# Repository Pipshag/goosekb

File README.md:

# Goose  38-key split wireless keyboard
Goose is a keyboard built with the help of [Ergogen](https://github.com/ergogen/ergogen).
This means that it's really simple to edit */config.yaml* and generate your own design, stagger and splay.
The KiCad PCBs are located in *pcb/* and contains the pcb, plate and bottom boards.
Use them to either manufacture directly or take leads from how I routed the pcb if you create your own. 

## Description
Wireless 38-key split and reversible keyboard with two rotary encoders, no support for button/press on these.
Plate is optional, but I'm using 3-pin switches which does almost make plates mandatory.
Batteries soldered directly to PCB, bought batteries with protection against shorts.
All PCBs are reversible.

Stagger and splay according to my hands, helped by [Ergopad](https://pashutk.com/ergopad/).
Artwork generated with Midjourney AI. Not really gooses but goose-like? :D

## Variations
See branches for keyswitch variations (choc and mx).

## Images
Final, completed, keyboard (left side).

Ergogen generated layout.

Routed PCB, KiCad preview.

## Materials
- 2 x Xiao Seeed nRF52840
- 2 x EC12 rotary encoders
- 2 x Knobs for rotary encoder
- 38 x Cherry MX switches
- 38 x SOD-123 Diodes
- 2 x LiPo batteries

## Firmware
ZMK firmware for wireless support. Contained in *firmware/*, includes build-script.

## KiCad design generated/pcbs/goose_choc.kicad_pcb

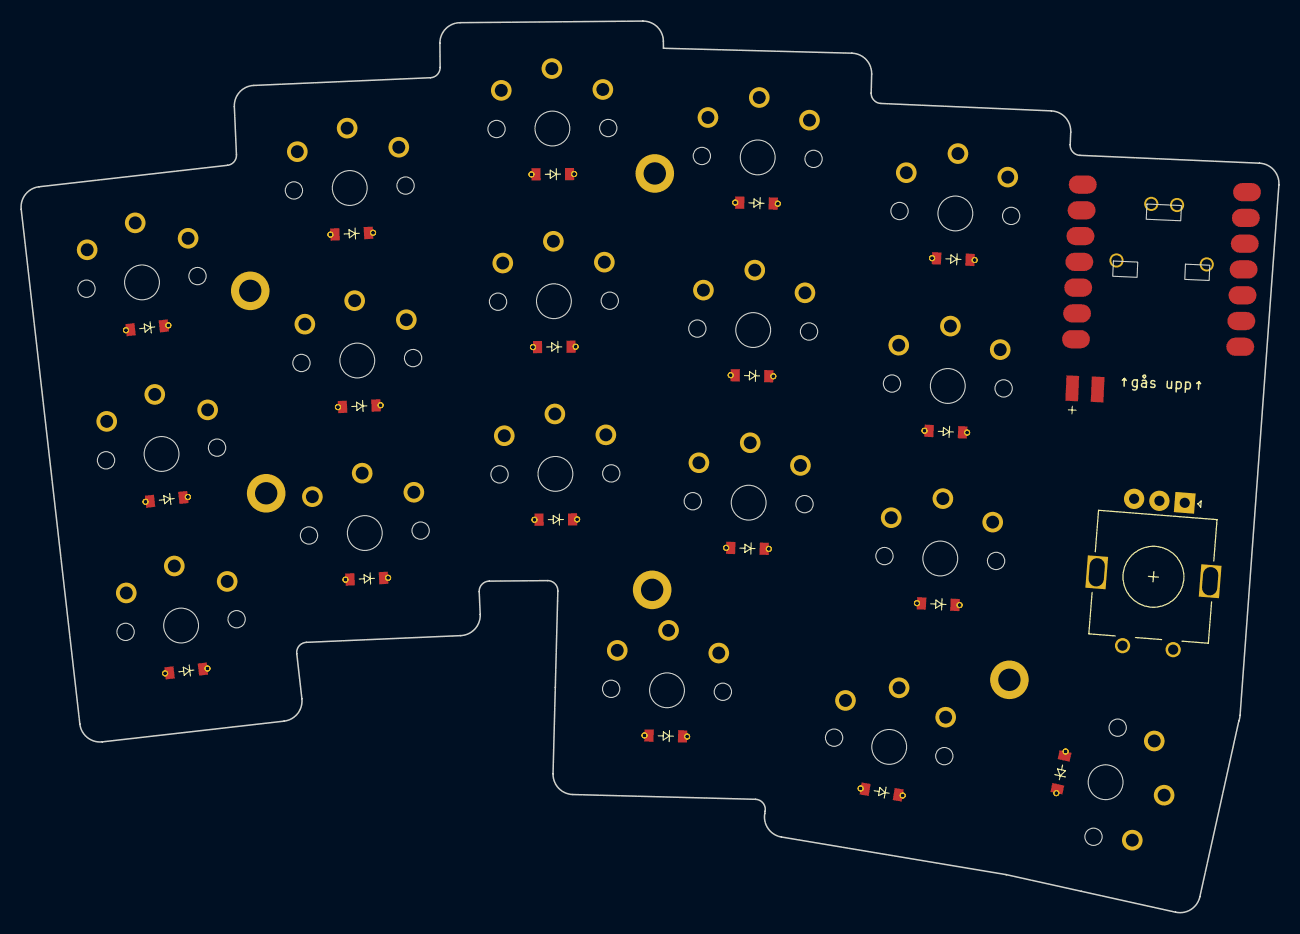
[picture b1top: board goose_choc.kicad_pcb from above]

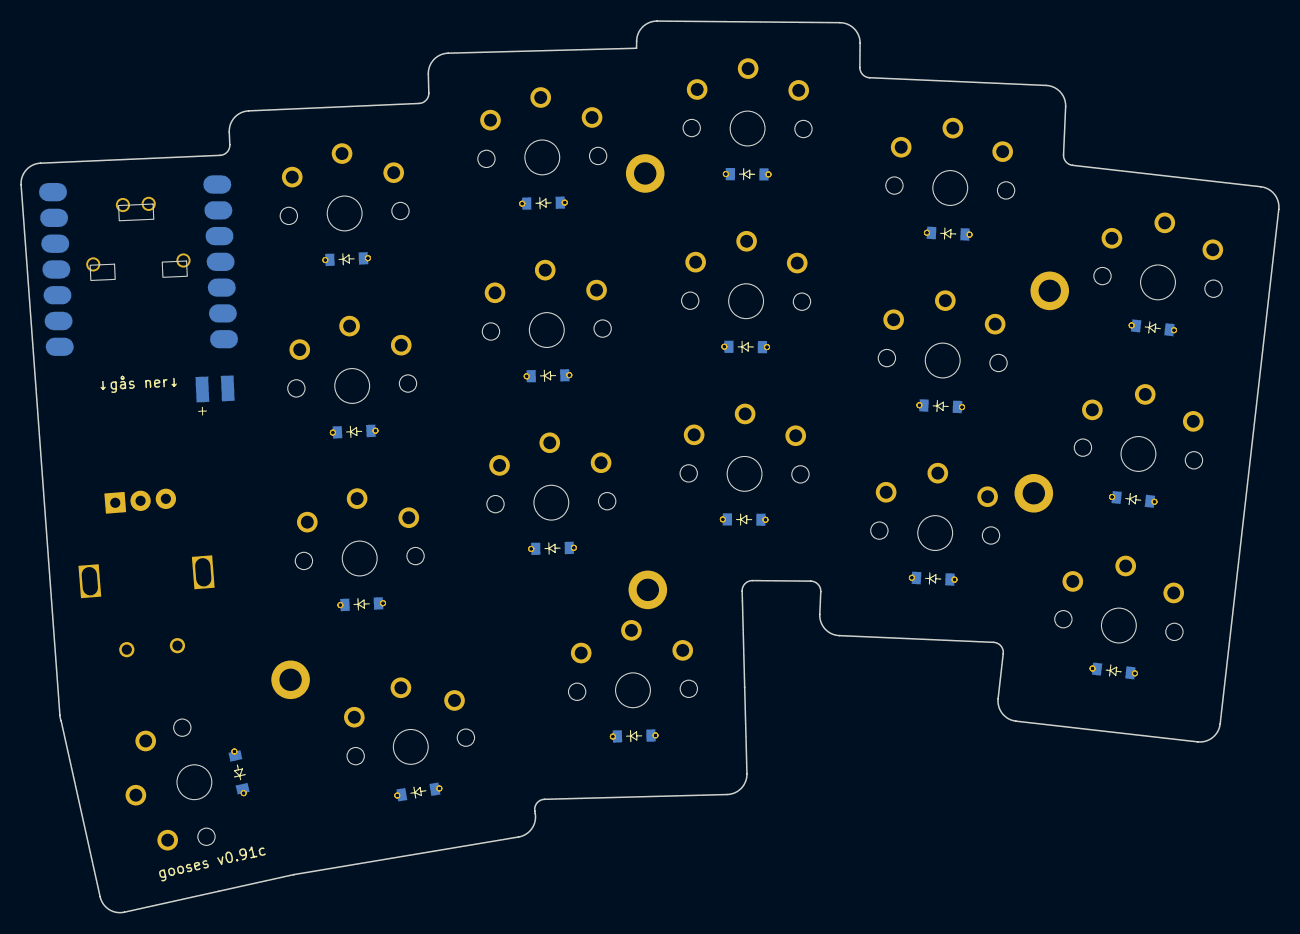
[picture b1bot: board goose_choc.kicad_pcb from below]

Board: 2 copper layers, 123.8 x 87.8 mm, 62 parts (18 on the bottom side), 31 nets, no tracks yet.

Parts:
Di1, Di2, Di3, Di4, Di5, Di6, Di7, Di8, Di9, Di10, Di11, Di12, Di13, Di14, Di15, Di16, Di17, Di18, Di19, Di20, Di21, Di22, Di23, Di24, Di25, Di26, Di27, Di28, Di29, Di30, Di31, Di32, Di33, Di34, Di35, Di36: D_SOD-123
H1, H2, H3, H4, H5: mounting_hole
MCU1: xiao-ble-smd-reversible
PAD1: pads
ROT1: rotary_encoder
S1, S2, S3, S4, S5, S6, S7, S8, S9, S10, S11, S12, S13, S14, S15, S16, S17, S18: PG1350

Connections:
BAT+: MCU1.19, PAD1.1, PAD1.2
C0: MCU1.1, S1.1, S2.1, S3.1
C0_R0: Di3.2, Di21.2, S3.2
C0_R1: Di2.2, Di20.2, S2.2
C0_R2: Di1.2, Di19.2, S1.2
C1: MCU1.2, S4.1, S5.1, S6.1, S16.1
C1_R0: Di6.2, Di24.2, S6.2
C1_R1: Di5.2, Di23.2, S5.2
C1_R2: Di4.2, Di22.2, S4.2
C1_R3: Di16.2, Di34.2, S16.2
C2: MCU1.3, S7.1, S8.1, S9.1, S17.1
C2_R0: Di9.2, Di27.2, S9.2
C2_R1: Di8.2, Di26.2, S8.2
C2_R2: Di7.2, Di25.2, S7.2
C2_R3: Di17.2, Di35.2, S17.2
C3: MCU1.4, S10.1, S11.1, S12.1, S18.1
C3_R0: Di12.2, Di30.2, S12.2
C3_R1: Di11.2, Di29.2, S11.2
C3_R2: Di10.2, Di28.2, S10.2
C3_R3: Di18.2, Di36.2, S18.2
C4: MCU1.5, S13.1, S14.1, S15.1
C4_R0: Di15.2, Di33.2, S15.2
C4_R1: Di14.2, Di32.2, S14.2
C4_R2: Di13.2, Di31.2, S13.2
ENCA: MCU1.8, ROT1.A
ENCB: MCU1.9, ROT1.B
GND: MCU1.13, MCU1.17, PAD1.1, PAD1.2, ROT1.C
R0: Di3.1, Di6.1, Di9.1, Di12.1, Di15.1, Di21.1, Di24.1, Di27.1, Di30.1, Di33.1, MCU1.6
R1: Di2.1, Di5.1, Di8.1, Di11.1, Di14.1, Di20.1, Di23.1, Di26.1, Di29.1, Di32.1, MCU1.7
R2: Di1.1, Di4.1, Di7.1, Di10.1, Di13.1, Di19.1, Di22.1, Di25.1, Di28.1, Di31.1, MCU1.11
R3: Di16.1, Di17.1, Di18.1, Di34.1, Di35.1, Di36.1, MCU1.10

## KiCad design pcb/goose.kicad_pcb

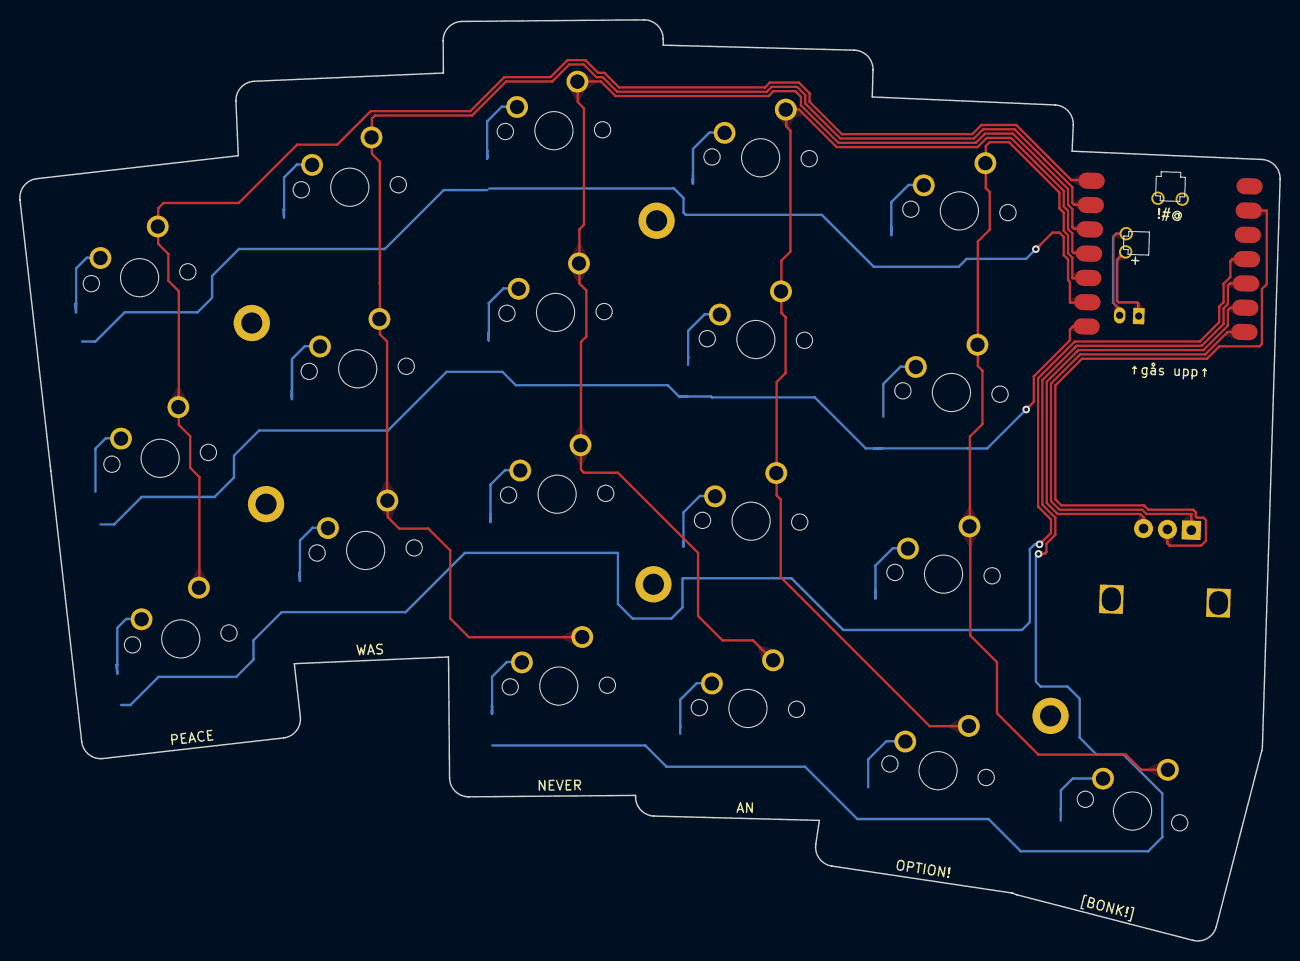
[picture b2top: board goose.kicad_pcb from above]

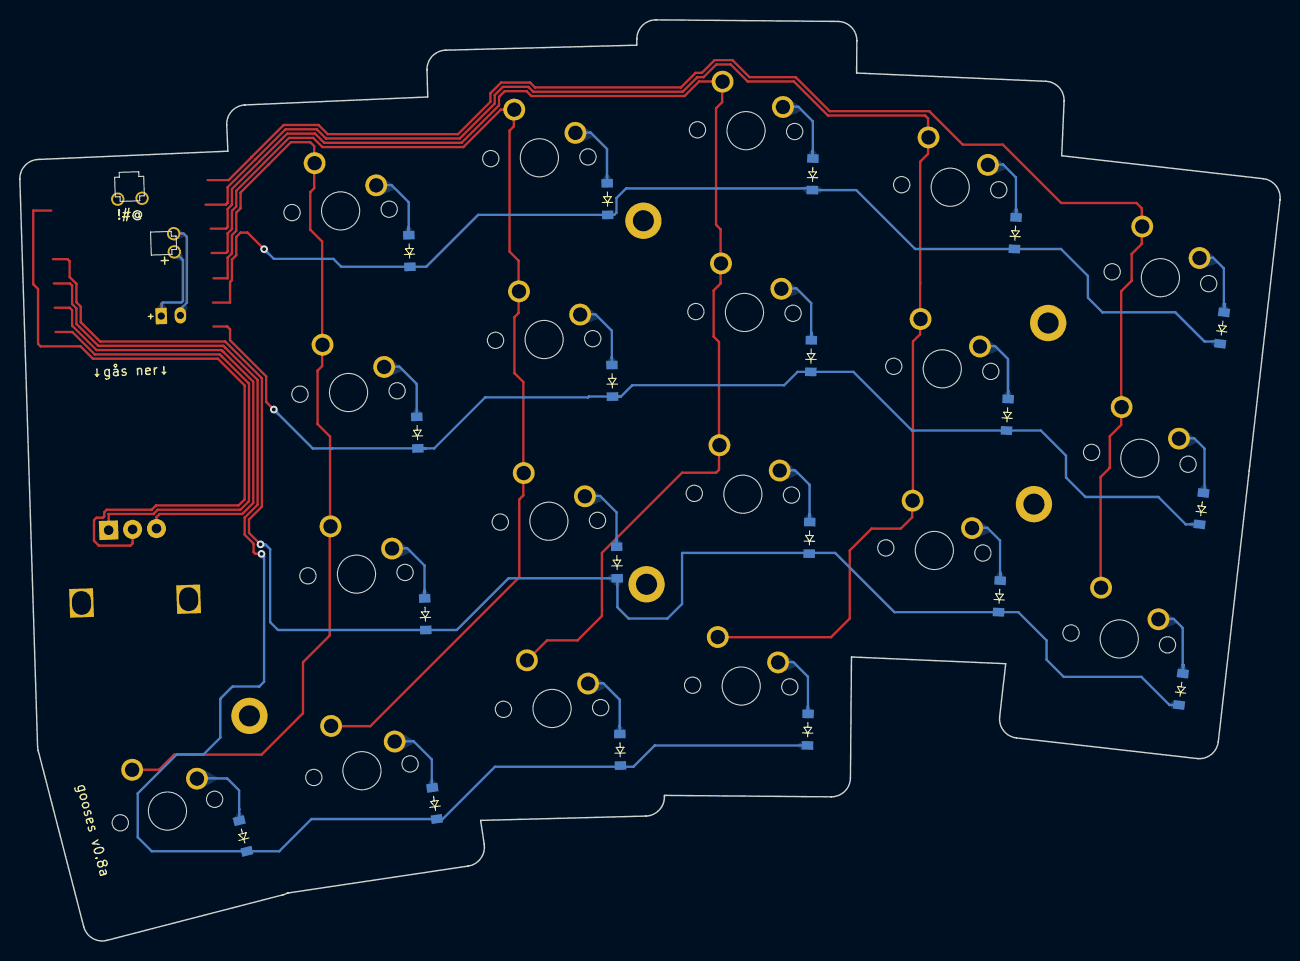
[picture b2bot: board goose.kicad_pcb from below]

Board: 2 copper layers, 131.7 x 96.3 mm, 46 parts (20 on the bottom side), 31 nets.

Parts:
BAT1: BatteryPad
Di1, Di2, Di3, Di4, Di5, Di6, Di7, Di8, Di9, Di10, Di11, Di12, Di13, Di14, Di15, Di16, Di17, Di18, Di19: D_SOD-123
H1, H2, H3, H4, H5: mounting_hole
ROT1: RotaryEncoder_Alps_EC12E_Vertical_H20mm
S1, S2, S3, S4, S5, S6, S7, S8, S9, S10, S11, S12, S13, S14, S15, S16, S17, S18, S19: MX
_1: Seeeduino XIAO nRF52840

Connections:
C0: S2.1, S10.1, S15.1, _1.1
C0_R0: Di7.2, S2.2
C0_R1: Di14.2, S10.2
C0_R2: Di19.2, S15.2
C1: S3.1, S4.1, S11.1, S17.1, _1.2
C1_R0: Di4.2, S4.2
C1_R1: Di11.2, S3.2
C1_R2: Di13.2, S11.2
C1_R3: Di18.2, S17.2
C2: S1.1, S5.1, S13.1, S16.1, _1.3
C2_R0: Di6.2, S1.2
C2_R1: Di5.2, S5.2
C2_R2: Di12.2, S13.2
C2_R3: Di17.2, S16.2
C3: S6.1, S7.1, S12.1, S18.1, _1.4
C3_R0: Di3.2, S7.2
C3_R1: Di2.2, S6.2
C3_R2: Di10.2, S12.2
C3_R3: Di16.2, S18.2
C4: S8.1, S9.1, S14.1, S19.1, _1.5
C4_R0: Di1.2, S9.2
C4_R1: Di9.2, S8.2
C4_R2: Di8.2, S14.2
C4_R3: Di15.2, S19.2
GND: ROT1.C, _1.13
P7: ROT1.A, _1.8
P8: ROT1.B, _1.9
R0: Di1.1, Di3.1, Di4.1, Di6.1, Di7.1, _1.6
R1: Di2.1, Di5.1, Di9.1, Di11.1, Di14.1, _1.7
R2: Di8.1, Di10.1, Di12.1, Di13.1, Di19.1, _1.11
R3: Di15.1, Di16.1, Di17.1, Di18.1, _1.10

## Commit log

2023-09-13 Initialize repo and WIP config of goosekb
2023-09-15 partial
2023-09-21 Almost finalized
2023-09-24 Ok version
2023-09-29 Mirrored pcbs
2023-10-01 Production
2023-10-02 Add initial ZMK firmware folders
2023-10-04 ZMK?
    Workflow test
    Update workflow
    Update build.yml
    Update build.yml
    Update build.yml
    Update build.yml
2023-10-04 Updated goose.keymap
2023-10-20 Updated goose.keymap Auto stash before merge of "master" and "origin/master"
    Updated goose.keymap
    Add debug fw-build paths
    Updated goose.keymap
    Updated goose.keymap
    Updated goose.keymap
    Updated goose.keymap
2023-10-20 Stage and test for keymap editor
2023-10-20 move zmk config for online keymap editor
2023-10-20 fix utility-buttons
2023-10-26 Start messing around with choc
2023-10-31 better tab
2023-11-03 re-organize tabs
2023-11-06 e89259f better tab
2023-11-15 Cherry Goose
2023-11-16 Choc pcb production ready
2023-11-20 Sleep, USB name
2023-11-20 Fix?
2023-12-06 Build script, disable deep sleep, tapping and key-repeat changes
2024-02-17 Mousekeys, media position on rotary
2024-05-23 Merge
2025-02-14 New homerow mods
2025-02-14 Testing homerowmods
2025-02-16 Still not satisfied
2025-02-16 Add back hold trigger keys
2025-02-16 Update
    Update
    Updated goose.keymap
    Update
    New homerow mods
    Testing homerowmods
    Still not satisfied
2025-02-16 Merge
    changes
2025-02-16 Update keymap, board name, and keyboard settings
    Keymap changes for various keys and behaviors. Renamed the board to "Goose Cherry" in configuration files. Adjusted default keyboard names in Kconfig.
2025-02-16 Cherry Goose run
    Use layout
    Updated goose.keymap
    Updated goose.keymap
2025-02-17 Looks ok
2025-02-20 Changes to home row mod timings
2025-05-08 Update README.md
    Clarified support for choc and mx switches
2025-05-08 Just a test
2025-08-06 Fix toggle back from layer
